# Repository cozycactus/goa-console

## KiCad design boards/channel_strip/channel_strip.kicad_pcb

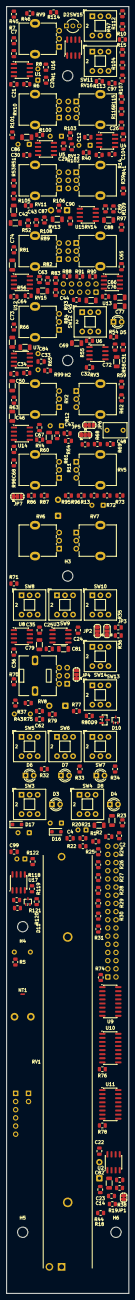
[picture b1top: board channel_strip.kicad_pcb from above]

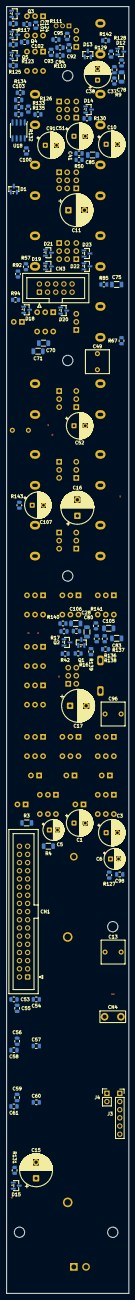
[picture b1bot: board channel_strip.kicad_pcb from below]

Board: 4 copper layers, 38.0 x 400.0 mm, 335 parts (105 on the bottom side), 195 nets, no tracks yet.

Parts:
C1, C3: 220u 25V; CP_Radial_D8.0mm_P3.50mm
C2, C4, C12, C20, C21, C22, C23, C24, C25, C26, C28, C29, C30, C31, C32, C33, C34, C35, C36, C53, C54, C55, C56, C57, C58, C59, C60, C61, C63, C64, C65, C66, C67, C68, C89, C90, C92, C93, C98, C100, C103, C104: 100n; C_0805_2012Metric
C5, C6: 47u 25V; CP_Radial_D6.3mm_P2.50mm
C7, C41: 33p C0G; C_0805_2012Metric
C10, C38, C51, C52, C91, C107: 33u NP 25V; CP_Radial_D8.0mm_P3.50mm
C11, C15, C16, C17: 100u NP 25V; CP_Radial_D10.0mm_P5.00mm
C13, C49, C96: 2.2u film; C_Rect_L7.2mm_W7.2mm_P5.00mm_FKS2_FKP2_MKS2_MKP2
C14, C94, C95: 100p C0G; C_0805_2012Metric
C37: 22p C0G; C_0805_2012Metric
C42, C43, C45: 4n7 C0G; C_1206_3216Metric
C44: 2n2 C0G; C_1206_3216Metric
C46: 10n C0G; C_1206_3216Metric
C47: 22n C0G; C_1206_3216Metric
C48: 150n film; C_Rect_L7.2mm_W4.5mm_P5.00mm_FKS2_FKP2_MKS2_MKP2
C50, C87, C88: 100n C0G; C_1206_3216Metric
C62: 1u; C_0805_2012Metric
C69, C70, C71, C72, C74, C76, C79, C80, C81, C82, C86: 10p C0G; C_1206_3216Metric
C73, C75, C77, C83, C85, C105, C106: 22p C0G; C_1206_3216Metric
C78: 33p C0G; C_1206_3216Metric
C84: 100p C0G; C_1206_3216Metric
C97, C99: 220n; C_0805_2012Metric
C101, C102: 10n; C_0805_2012Metric
CN1: Bus 2x17; IDC-Header_2x17_P2.54mm_Vertical
CN3: Jack board link 2x5; IDC-Header_2x05_P2.54mm_Vertical
CN4: Ground spade 6.3mm; Keystone_1287-ST_FastOn_Tab_6.35mm
D1, D12, D13, D14, D15: BAV99; SOT-23
D2: OL red / SIG green; LED_D3.0mm-3_P2.00mm
D3: PFL red; LED_D3.0mm
D4: ON green; LED_D3.0mm
D5: EQ green; LED_D3.0mm
D6: L-R yellow; LED_D3.0mm
D7: 1-2 yellow; LED_D3.0mm
D8: 3-4 yellow; LED_D3.0mm
D9: BZX84C5V1; SOT-23
D10, D11: BAT54W; SOT-323_SC-70
D16, D17: MBR140SFT1G; D_SOD-123F
D18, D19, D20, D21, D22, D23: BAV199; SOT-23
H1, H2, H3, H4, H5, H6: M3 standoff 11.5 mm; MountingHole_3.2mm_M3
J3: VCA module socket; PinSocket_1x06_P2.54mm_Vertical
J4: VCA control in; PinHeader_1x02_P2.54mm_Vertical
JP1: VCA bypass; SolderJumper-2_P1.3mm_Bridged_RoundedPad1.0x1.5mm
JP2: Aux1/2 pre source; SolderJumper-3_P1.3mm_Bridged12_RoundedPad1.0x1.5mm
JP3: Aux3/4 pre source; SolderJumper-3_P1.3mm_Bridged12_RoundedPad1.0x1.5mm
JP4: Aux5/6 pre source; SolderJumper-3_P1.3mm_Bridged12_RoundedPad1.0x1.5mm
JP5: Insert send source; SolderJumper-3_P1.3mm_Bridged12_RoundedPad1.0x1.5mm
JP6: EQ input; SolderJumper-3_P1.3mm_Bridged12_RoundedPad1.0x1.5mm
JP7: PRE source; SolderJumper-3_P1.3mm_Bridged12_RoundedPad1.0x1.5mm
NT1: AGND-LGND star; NetTie-2_SMD_Pad0.5mm
Q1, Q2: MMBFJ112; SOT-23
Q3, Q4, Q5: MMBT3906; SOT-23
R1, R2, R3, R4: 10R; R_1206_3216Metric
R5: 10R GND cancel; R_0805_2012Metric
R6, R7, R8, R9: 10K 0.1%; R_0805_2012Metric
R10, R112, R115, R121, R142: 1M; R_0805_2012Metric
R11, R71, R73: 75R; R_0805_2012Metric
R12, R13, R35, R36, R37, R47, R68, R72, R116, R117, R118, R122, R123, R125, R143: 47K; R_0805_2012Metric
R14, R134: 470K; R_0805_2012Metric
R15, R16, R17, R19, R34, R43, R69, R75, R77, R79, R80, R124: 4K7; R_0805_2012Metric
R18, R33, R44, R70, R74, R76, R78: 100K; R_0805_2012Metric
R20, R21, R22, R23, R24, R25, R32, R54, R55, R58, R59, R66, R67: 22K; R_0805_2012Metric
R26, R27, R28, R29, R30, R31: 4K7 1%; R_0805_2012Metric
R38, R137, R140: 2K2; R_0805_2012Metric
R39, R99, R126, R127, R128, R129, R130, R131, R135: 1K; R_0805_2012Metric
R40, R41, R120, R138, R141: 10K; R_0805_2012Metric
R42: 220K; R_0805_2012Metric
R45, R46, R84, R93: 2K2 1%; R_0805_2012Metric
R50, R51: 33K; R_0805_2012Metric
R52: 5K6; R_0805_2012Metric
R53: 6K8; R_0805_2012Metric
R56, R57, R100, R103: 4K99 1%; R_0805_2012Metric
R60, R61: 4K22 1%; R_0805_2012Metric
R62, R63, R136, R139: 3K3; R_0805_2012Metric
R64: 1K5; R_0805_2012Metric
R65: 5K1; R_0805_2012Metric
R81, R82, R83, R85, R90, R91, R92, R94: 10K 1%; R_0805_2012Metric
R86, R87: 392R 1%; R_0805_2012Metric
R88, R89, R97, R98, R105, R108: 13K 1%; R_0805_2012Metric
R95, R96: 430R 1%; R_0805_2012Metric
R101, R102: 2K49 1%; R_0805_2012Metric
R104, R107: 330R 1%; R_0805_2012Metric
R106, R109: 5K6 1%; R_0805_2012Metric
R110, R111: 220R; R_0805_2012Metric
R113, R114: 100R; R_0805_2012Metric
R119: 750K; R_0805_2012Metric
R132: 4M99 1%; R_0805_2012Metric
R133: 10M 1%; R_0805_2012Metric
RV1: Fader 10K log 100mm; Potentiometer_Bourns_PTB0143_Slide_100mm
RV2: Aux1 10K log; Potentiometer_Alpha_RD901F-40-00D_Single_Vertical
RV3: Aux2 10K log; Potentiometer_Alpha_RD901F-40-00D_Single_Vertical
RV4: Aux3 10K log; Potentiometer_Alpha_RD901F-40-00D_Single_Vertical
RV5: Aux4 10K log; Potentiometer_Alpha_RD901F-40-00D_Single_Vertical
RV6: Aux5 10K log; Potentiometer_Alpha_RD901F-40-00D_Single_Vertical
RV7: Aux6 10K log; Potentiometer_Alpha_RD901F-40-00D_Single_Vertical
RV8: Pan 10K lin dual CD; Potentiometer_Alps_RK09L_Double_Vertical
RV9: Gain 10K lin CD; Potentiometer_Alpha_RD901F-40-00D_Single_Vertical
RV10: HF 10K lin CD; Potentiometer_Alpha_RD901F-40-00D_Single_Vertical
RV11: HI-MID gain 10K lin CD; Potentiometer_Alpha_RD901F-40-00D_Single_Vertical
RV12: HI-MID freq 10K A dual; Potentiometer_Alpha_RD902F-40-00D_Dual_Vertical
RV13: LO-MID gain 10K lin CD; Potentiometer_Alpha_RD901F-40-00D_Single_Vertical
RV14: LO-MID freq 10K A dual; Potentiometer_Alpha_RD902F-40-00D_Dual_Vertical
RV15: LF 10K lin CD; Potentiometer_Alpha_RD901F-40-00D_Single_Vertical
RV16: HPF freq 10K A dual; Potentiometer_Alpha_RD902F-40-00D_Dual_Vertical
SW3: PFL; SW_Push_2P2T_Toggle_CK_PVA2xxH1xxxxxxV2
SW4: ON; SW_Push_2P2T_Toggle_CK_PVA2xxH1xxxxxxV2
SW5: Assign L-R; SW_Push_2P2T_Toggle_CK_PVA2xxH1xxxxxxV2
SW6: Assign 1-2; SW_Push_2P2T_Toggle_CK_PVA2xxH1xxxxxxV2
SW7: Assign 3-4; SW_Push_2P2T_Toggle_CK_PVA2xxH1xxxxxxV2
SW8: PRE 1-2; SW_Push_2P2T_Toggle_CK_PVA2xxH1xxxxxxV2
SW9: PRE 3-4; SW_Push_2P2T_Toggle_CK_PVA2xxH1xxxxxxV2
SW10: PRE 5-6; SW_Push_2P2T_Toggle_CK_PVA2xxH1xxxxxxV2
SW11: HPF; SW_Push_2P2T_Toggle_CK_PVA2xxH1xxxxxxV2
SW12: EQ; SW_Push_2P2T_Toggle_CK_PVA2xxH1xxxxxxV2
SW13: DIR; SW_Push_2P2T_Toggle_CK_PVA2xxH1xxxxxxV2
SW14: PAN; SW_Push_2P2T_Toggle_CK_PVA2xxH1xxxxxxV2
SW15: Phase; SW_Push_2P2T_Toggle_CK_PVA2xxH1xxxxxxV2
U1, U2, U3, U5, U6, U7, U8, U12, U13, U14, U15: OPA1612; SOIC-8_3.9x4.9mm_P1.27mm
U4, U17, U18: LM393; SOIC-8_3.9x4.9mm_P1.27mm
U9, U10, U11: DG413; SOIC-16_3.9x9.9mm_P1.27mm
U16: OPA1656; SOIC-8_3.9x4.9mm_P1.27mm

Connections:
+5VL: C55.1, C58.1, C61.1, C62.1, D9.3, D10.1, R80.2, SW5.1, SW6.1, SW7.1, U9.12, U10.12, U11.12
+VA: C1.1, C2.1, C20.1, C22.1, C24.1, C29.1, C31.1, C33.1, C35.1, C53.1, C56.1, C59.1, C63.1, C65.1, C67.1, C89.1, C92.1, D10.3, D16.1, D18.2, D19.2, D20.2, D21.2, D22.2, D23.2, J3.4, R1.2, R80.1, U1.8, U2.8, U3.8, U5.8, U6.8, U7.8, U8.8, U9.13, U10.13, U11.13, U12.8, U13.8, U14.8, U15.8, U16.8
+VBUS: CN1.32, CN1.33, CN1.34, R1.1, R3.1
+VL: C5.1, C26.1, C98.1, C101.2, C102.2, C104.1, Q3.2, Q4.2, Q5.2, R3.2, R40.1, R115.1, R117.1, R121.1, R123.1, R132.1, SW3.5, SW4.5, SW5.5, SW6.5, SW7.5, SW12.5, U4.8, U17.8, U18.8
-VA: C3.2, C4.2, C21.2, C23.2, C25.2, C30.2, C32.2, C34.2, C36.2, C54.2, C57.2, C60.2, C64.2, C66.2, C68.2, C90.2, C93.2, D17.2, D18.1, D19.1, D20.1, D21.1, D22.1, D23.1, J3.6, R2.2, U1.4, U2.4, U3.4, U5.4, U6.4, U7.4, U8.4, U9.4, U10.4, U11.4, U12.4, U13.4, U14.4, U15.4, U16.4
-VBUS: CN1.30, CN1.31, R2.1, R4.1
-VL: C6.2, R4.2, SW4.1
A6R: R25.1, SW13.3, SW13.5
AUX1: CN1.24, R20.2
AUX2: CN1.25, R21.2
AUX3: CN1.23, R22.2
AUX4: CN1.22, R23.2
AUX5: CN1.21, R24.2
AUX6: CN1.20, R25.2
BUF1: JP6.3, JP7.1, U7.6, U7.7
DIRSRC: C83.1, R70.1, SW13.1, U8.3
DO_R: CN3.9, D23.3, R73.1, R143.1
DO_T: C52.2, CN3.8, D22.3, R72.1
EQIN: JP6.2, R50.1, RV10.3, SW12.3
EQOUT: C51.2, JP5.1, JP7.3, R68.1, R130.1
EQ_FP: C49.2, C50.1, R65.1, U7.3
EQ_LP: C46.1, R93.1, R98.1, RV14.6, U6.5, U14.1
EQ_MP: C44.1, R84.1, R89.1, RV12.6, U6.3, U12.7
EQ_O6: C73.1, R63.2, R67.1, SW12.1, U7.1
EQ_WHM: R81.1, RV11.2
EQ_WLM: R90.1, RV13.2
FPIN: C82.1, J3.2, JP1.2, R18.1, U2.3
FPOST: C14.1, C15.1, R19.1, R131.1, U2.1
GCANCEL: CN1.26, R5.2
GNDA: C1.2, C2.2, C3.1, C4.1, C12.2, C20.2, C21.1, C22.2, C23.1, C24.2, C25.1, C28.2, C29.2, C30.1, C31.2, C32.1, C33.2, C34.1, C35.2, C36.1, C50.2, C53.2, C54.1, C56.2, C57.1, C59.2, C60.1, C63.2, C64.1, C65.2, C66.1, C67.2, C68.1, C75.2, C77.2, C78.2, C79.2, C80.2, C81.2, C82.2, C83.2, C84.2, C85.2, C89.2, C90.1, C92.2, C93.1, C94.2, C95.2, C100.2, C103.2, C107.2, CN1.2, CN1.4, CN1.6, CN1.8, CN1.10, CN1.12, CN1.14, CN1.16, CN3.3, CN3.5, CN3.7, CN3.10, CN4.1, D16.2, D17.1, J3.5, J4.2, NT1.1, Q1.2, Q2.2, R5.1, R9.2, R10.2, R12.2, R13.2, R14.2, R18.2, R35.2, R36.2, R37.2, R38.2, R41.2, R44.2, R47.2, R52.2, R65.2, R68.2, R70.2, R72.2, R85.2, R86.2, R87.2, R94.2, R95.2, R96.2, R104.2, R107.2, R112.2, R120.2, R134.2, R138.1, R141.1, R143.2, RV1.1, RV2.1, RV3.1, RV4.1, RV5.1, RV6.1, RV7.1, RV8.3, RV8.4, SW3.3, SW13.4, U1.5, U2.5, U5.5, U9.10, U9.15, U10.10, U10.15, U11.10, U11.15, U12.5, U13.3, U14.3, U14.5, U15.3, U15.5
GNDD: C5.2, C6.1, C26.2, C55.2, C58.2, C61.2, C62.2, C97.2, C98.2, C99.2, C104.2, D2.2, D3.1, D4.1, D5.1, D6.1, D7.1, D8.1, D9.1, D11.1, NT1.2, R74.2, R76.2, R78.2, SW4.3, SW5.3, SW6.3, SW7.3, U4.4, U9.5, U10.5, U11.5, U17.4, U18.4, U18.6
GOUT: C37.1, C38.1, C91.1, R46.2, R129.1, R142.2, U1.7
HIN: C38.2, C91.2, R47.1, R100.1, SW11.3
HOUT: JP2.3, JP3.3, JP4.3, JP5.3, JP6.1, SW11.2
INS_SRC: JP5.2, R11.1
IN_R: CN3.2, D19.3, R111.1, R112.1
IN_T: CN3.1, D18.3, R10.1, R110.1
MIXL: CN1.18, U9.2
MIXR: CN1.17, U9.7
MUTEOUT: JP2.1, JP3.1, JP4.1, RV1.3, U3.6, U3.7
unnamed: C10.2, R12.1, R99.1
unnamed: C13.1, RV1.2
unnamed: C41.1, C69.1, R51.1, R54.1, RV10.1, RV11.1, U5.7
unnamed: C42.1, RV10.2
unnamed: C42.2, C43.1, R52.1
unnamed: C43.2, R53.1
unnamed: C45.1, R82.1, U13.1
unnamed: C47.1, R91.1, U14.7
unnamed: C48.1, R62.2, RV15.1
unnamed: C48.2, R63.1, RV15.3
unnamed: C49.1, R64.2
unnamed: C52.1, R71.2
unnamed: C70.1, C71.1, R55.1, R58.1, RV11.3, RV13.1, U6.1
unnamed: C72.1, R59.1, R62.1, R66.1, RV13.3, U6.7
unnamed: C74.1, R83.1, R88.1, RV12.3, U12.1
unnamed: C76.1, R92.1, R97.1, RV14.3, U13.7
unnamed: C87.1, R101.1, R108.1, RV16.6, U15.1
unnamed: C88.1, R102.1, U15.7
unnamed: C96.2, R32.1
unnamed: C16.1, C105.2, R136.1, R137.2, U8.7
unnamed: C17.1, C106.2, R139.1, R140.2, U3.1
unnamed: C107.1, R73.2
unnamed: D1.3, R39.2
unnamed: D3.2, R34.2
unnamed: D4.2, R43.2
unnamed: D5.2, R69.2
unnamed: D6.2, R75.2
unnamed: D7.2, R77.2
unnamed: D8.2, R79.2
unnamed: D12.3, R128.2
unnamed: D13.3, R129.2
unnamed: D14.3, R130.2
unnamed: D15.3, R131.2
unnamed: JP2.2, SW8.1
unnamed: JP3.2, SW9.1
unnamed: JP4.2, SW10.1
unnamed: Q1.1, R16.2, R17.1
unnamed: C28.1, Q1.3, Q2.3, R42.2
unnamed: C81.1, Q2.1, R17.2, U3.5
unnamed: C101.1, Q3.1, R116.2, R117.2
unnamed: Q3.3, R15.1
unnamed: Q4.3, R124.1
unnamed: Q5.1, R125.2
unnamed: R20.1, RV2.2
unnamed: R21.1, RV3.2
unnamed: R22.1, RV4.2
unnamed: R23.1, RV5.2
unnamed: R24.1, RV6.2
unnamed: R26.2, U9.3, U9.14
unnamed: R27.2, U9.6, U9.11
unnamed: R28.2, U10.3, U10.14
unnamed: R29.2, U10.6, U10.11
unnamed: R30.2, U11.3, U11.14
unnamed: R31.2, U11.6, U11.11
unnamed: R45.2, RV9.3
unnamed: R46.1, RV9.1
unnamed: R56.1, R88.2, RV12.2
unnamed: R57.1, R89.2, RV12.5
unnamed: R60.1, R97.2, RV14.2
unnamed: R61.1, R98.2, RV14.5
unnamed: R64.1, RV15.2
unnamed: R86.1, RV12.1
unnamed: R87.1, RV12.4
unnamed: R95.1, RV14.1
unnamed: R96.1, RV14.4
unnamed: R104.1, RV16.1
unnamed: R105.2, R106.1, RV16.2
unnamed: R107.1, RV16.4
unnamed: R108.2, R109.1, RV16.5
unnamed: R122.1, U17.7
unnamed: R126.1, U4.1
unnamed: R127.1, U17.1
unnamed: R135.1, U18.1
unnamed: R32.2, SW3.2
unnamed: R33.1, R34.1, SW3.4
unnamed: R42.1, SW4.2
unnamed: R43.1, SW4.4
unnamed: R75.1, SW5.4
unnamed: R77.1, SW6.4
unnamed: R79.1, SW7.4
unnamed: RV2.3, RV3.3, SW8.2
unnamed: RV4.3, RV5.3, SW9.2
unnamed: RV6.3, RV7.3, SW10.2
unnamed: C86.1, R103.1, R105.1, RV16.3, SW11.1, U5.1
unnamed: C51.1, SW12.2
unnamed: R69.1, SW12.4
unnamed: RV7.2, SW13.2
unnamed: R114.2, SW15.1, SW15.6
unnamed: R6.1, SW15.2
unnamed: R113.2, SW15.3, SW15.4
unnamed: R8.1, SW15.5
unnamed: C78.1, R8.2, R9.1, U1.3
unnamed: C7.1, R6.2, R7.1, U1.2
unnamed: C37.2, R142.1, RV9.2, U1.6
unnamed: C14.2, R19.2, R38.1, U2.2
unnamed: U2.6, U2.7
unnamed: C80.1, R139.2, RV8.5, U3.3
unnamed: C106.1, R140.1, R141.2, U3.2
unnamed: C85.1, R100.2, R101.2, U5.3
unnamed: C86.2, R102.2, R103.2, U5.2
unnamed: C41.2, R50.2, R51.2, R53.2, U5.6
unnamed: C69.2, C70.2, R54.2, R55.2, U6.2
unnamed: C71.2, C72.2, R58.2, R59.2, U6.6
unnamed: C73.2, R66.2, R67.2, U7.2
unnamed: C84.1, R99.2, U7.5
unnamed: R71.1, U8.1, U8.2
unnamed: C79.1, R136.2, RV8.2, U8.5
unnamed: C105.1, R137.1, R138.2, U8.6
unnamed: C75.1, R84.2, R85.1, U12.3
unnamed: C74.2, R81.2, R82.2, R83.2, U12.2
unnamed: C44.2, R56.2, U12.6
unnamed: C45.2, R57.2, U13.2
unnamed: C77.1, R93.2, R94.1, U13.5
unnamed: C76.2, R90.2, R91.2, R92.2, U13.6
unnamed: C46.2, R60.2, U14.2
unnamed: C47.2, R61.2, U14.6
unnamed: C87.2, R106.2, U15.2
unnamed: C88.2, R109.2, U15.6
unnamed: C94.1, R110.2, U16.3
unnamed: R113.1, U16.1, U16.2
unnamed: C95.1, R111.2, U16.5
unnamed: R114.1, U16.6, U16.7
unnamed: R119.2, R120.1, U17.3
unnamed: C99.1, R121.2, R127.2, U17.5
unnamed: R132.2, R133.1, U18.3
OL_A: D2.1, R15.2
OL_HOLD: C97.1, R115.2, R126.2, R135.2, U4.5
OL_K: R116.1, R125.1, U4.7
OL_NN: C103.1, D1.1, D12.1, D13.1, D14.1, D15.1, R133.2, R134.1
PANL: C16.2, R26.1, R36.1, SW14.1
PANR: C17.2, R27.1, R37.1, SW14.4
PFL: CN1.27, SW3.1
PFLDET: CN1.29, R33.2
PK: C12.1, D1.2, D12.2, D13.2, D14.2, D15.2, R14.1, U4.2
POST: C15.2, R35.1, RV8.1, RV8.6, SW8.3, SW9.3, SW10.3, SW14.3, SW14.6
PRE: C11.2, C96.1, R13.1, R16.1
PRESRC: C11.1, JP7.2, R39.1, R118.1
RECV: C7.2, R7.2, R45.1, R128.1, U1.1
RET_RAW: C10.1, CN3.6, D20.3
RTE_12: R76.1, SW6.2, U10.1, U10.8, U10.9, U10.16
RTE_34: R78.1, SW7.2, U11.1, U11.8, U11.9, U11.16
RTE_LR: R74.1, SW5.2, U9.1, U9.8, U9.9, U9.16
SEND: CN3.4, D21.3, R11.2
SIG_A: D2.3, R124.2
SIG_B: C102.1, Q4.1, Q5.3, R122.2, R123.2
SIG_IN: D11.3, R118.2, U17.2
SUB1: CN1.15, U10.2
SUB2: CN1.13, U10.7
SUB3: CN1.11, U11.2
SUB4: CN1.9, U11.7
SUBSRC_L: R28.1, R30.1, SW14.2
SUBSRC_R: R29.1, R31.1, SW14.5
VCAIN: C13.2, J3.1, JP1.1
VCA_CTRL: J3.3, J4.1, R44.1
VREF: C100.1, R40.2, R41.1, R119.1, U4.3, U4.6, U17.6, U18.2, U18.5

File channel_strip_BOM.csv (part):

"Qty","Value","Footprint","MPN","DNP","References"
"2","220u 25V","Capacitor_THT:CP_Radial_D8.0mm_P3.50mm","Rubycon 35ZLH220MEFC8X11.5 (35V)","","C1 C3"
"38","100n","Capacitor_SMD:C_0805_2012Metric","Samsung CL21B104KBCNNNC (X7R 50V)","","C2 C4 C12 C20 C21 C22 C23 C24 C25 C26 C28 C29 C30 C31 C32 C33 C34 C35 C36 C53 C54 C55 C56 C57 C58 C59 C60 C61 C63 C64 C65 C66 C67 C68 C89 C90 C92 C93"
"2","47u 25V","Capacitor_THT:CP_Radial_D6.3mm_P2.50mm","Panasonic EEU-FR1H470 (50V)","","C5 C6"
"2","33p C0G","Capacitor_SMD:C_0805_2012Metric","KEMET C1206C330J5GACTU","","C7 C41"
"5","33u NP 25V","Capacitor_THT:CP_Radial_D8.0mm_P3.50mm","Nichicon UES1E330MPM (MUSE ES)","","C10 C38 C51 C52 C91"
"4","100u NP 25V","Capacitor_THT:CP_Radial_D10.0mm_P5.00mm","Nichicon UES1E101MPM (MUSE ES)","","C11 C15 C16 C17"
"3","2.2u film","Capacitor_THT:C_Rect_L7.2mm_W7.2mm_P5.00mm_FKS2_FKP2_MKS2_MKP2","WIMA MKS2C042201K00KSSD (PET 63V)","","C13 C49 C96"
"3","100p C0G","Capacitor_SMD:C_0805_2012Metric","KEMET C1206C101J5GACTU","","C14 C94 C95"
"1","22p C0G","Capacitor_SMD:C_0805_2012Metric","KEMET C1206C220J5GACTU","","C37"
"3","4n7 C0G","Capacitor_SMD:C_1206_3216Metric","KEMET C1206C472J5GACTU","","C42 C43 C45"
"1","2n2 C0G","Capacitor_SMD:C_1206_3216Metric","KEMET C1206C222J5GACTU","","C44"
"1","10n C0G","Capacitor_SMD:C_1206_3216Metric","KEMET C1206C103J5GACTU","","C46"
"1","22n C0G","Capacitor_SMD:C_1206_3216Metric","KEMET C1206C223J5GACTU","","C47"
"1","150n film","Capacitor_THT:C_Rect_L7.2mm_W4.5mm_P5.00mm_FKS2_FKP2_MKS2_MKP2","WIMA MKS2D031501C00KSSD (PET 100V; 3.5 x 8.5 x 7.2, the 63 V KSSD code has no stock)","","C48"
"3","100n C0G","Capacitor_SMD:C_1206_3216Metric","Murata GRM31C5C1H104JA01L","","C50 C87 C88"
"1","1u","Capacitor_SMD:C_0805_2012Metric","Murata GRM21BR71H105KA12L (X7R 50V)","","C62"
"11","10p C0G","Capacitor_SMD:C_1206_3216Metric","KEMET C1206C100J5GACTU","","C69 C70 C71 C72 C74 C76 C79 C80 C81 C82 C86"
"5","22p C0G","Capacitor_SMD:C_1206_3216Metric","KEMET C1206C220J5GACTU","","C73 C75 C77 C83 C85"
"1","33p C0G","Capacitor_SMD:C_1206_3216Metric","KEMET C1206C330J5GACTU","","C78"
"1","100p C0G","Capacitor_SMD:C_1206_3216Metric","KEMET C1206C101J5GACTU","","C84"
"1","220n","Capacitor_SMD:C_0805_2012Metric","Samsung CL21B224KBFNNNE (X7R 50V)","","C97"
"1","Bus 2x17","Connector_IDC:IDC-Header_2x17_P2.54mm_Vertical","Wurth 61203421621 (2x17 box header)","","CN1"
"1","Jack board link 2x5","Connector_IDC:IDC-Header_2x05_P2.54mm_Vertical","Wurth 61201021621 (2x5 box header)","","CN3"
"1","Ground spade 6.3mm","goa-console:Keystone_1287-ST_FastOn_Tab_6.35mm","Keystone 1287-ST","","CN4"
"1","1N4148","Diode_THT:D_DO-35_SOD27_P7.62mm_Horizontal","Vishay 1N4148-TAP","","D1"
"1","OL red","LED_THT:LED_D3.0mm","Kingbright WP710A10ID","","D2"
"1","PFL red","LED_THT:LED_D3.0mm","Kingbright WP710A10ID","","D3"
"1","ON green","LED_THT:LED_D3.0mm","Kingbright WP710A10GD","","D4"
"1","EQ green","LED_THT:LED_D3.0mm","Kingbright WP710A10GD","","D5"
"1","L-R yellow","LED_THT:LED_D3.0mm","Kingbright WP710A10YD","","D6"
"1","1-2 yellow","LED_THT:LED_D3.0mm","Kingbright WP710A10YD","","D7"
"1","3-4 yellow","LED_THT:LED_D3.0mm","Kingbright WP710A10YD","","D8"
"1","BZX84C5V1","Package_TO_SOT_SMD:SOT-23","Nexperia BZX84-C5V1,215","","D9"
"1","BAT54W","Package_TO_SOT_SMD:SOT-323_SC-70","Nexperia BAT54W,115","","D10"
"1","VCA module socket","Connector_PinSocket_2.54mm:PinSocket_1x06_P2.54mm_Vertical","","DNP","J3"
"1","VCA control in","Connector_PinHeader_2.54mm:PinHeader_1x02_P2.54mm_Vertical","","DNP","J4"
"2","MMBFJ112","Package_TO_SOT_SMD:SOT-23","onsemi MMBFJ112","","Q1 Q2"
"2","10R","Resistor_SMD:R_0805_2012Metric","Panasonic ERJ-P06J100V","","R1 R2"
"2","10R","Resistor_SMD:R_0805_2012Metric","","","R3 R4"
"1","10R GND cancel","Resistor_SMD:R_0805_2012Metric","","","R5"
"4","10K 0.1%","Resistor_SMD:R_0805_2012Metric","Panasonic ERA-6AEB103V","","R6 R7 R8 R9"
"3","1M","Resistor_SMD:R_0805_2012Metric","","","R10 R112 R115"
"2","75R","Resistor_SMD:R_0805_2012Metric","Panasonic ERJ-P06J750V","","R11 R71"
"8","47K","Resistor_SMD:R_0805_2012Metric","","","R12 R13 R35 R36 R37 R47 R68 R72"
"1","470K","Resistor_SMD:R_0805_2012Metric","","","R14"
"11","4K7","Resistor_SMD:R_0805_2012Metric","","","R15 R16 R17 R19 R34 R43 R69 R75 R77 R79 R80"
"6","100K","Resistor_SMD:R_0805_2012Metric","","","R18 R33 R70 R74 R76 R78"
"13","22K","Resistor_SMD:R_0805_2012Metric","","","R20 R21 R22 R23 R24 R25 R32 R54 R55 R58 R59 R66 R67"
"10","4K7 1%","Resistor_SMD:R_0805_2012Metric","","","R26 R27 R28 R29 R30 R31 R56 R57 R60 R61"
"1","2K2","Resistor_SMD:R_0805_2012Metric","","","R38"
"2","1K","Resistor_SMD:R_0805_2012Metric","","","R39 R99"
"2","10K","Resistor_SMD:R_0805_2012Metric","","","R40 R41"
"1","220K","Resistor_SMD:R_0805_2012Metric","","","R42"
"1","100K","Resistor_SMD:R_0805_2012Metric","","DNP","R44"
"4","2K2 1%","Resistor_SMD:R_0805_2012Metric","","","R45 R46 R84 R93"
"2","33K","Resistor_SMD:R_0805_2012Metric","","","R50 R51"
"1","5K6","Resistor_SMD:R_0805_2012Metric","","","R52"
"1","6K8","Resistor_SMD:R_0805_2012Metric","","","R53"
"2","3K3","Resistor_SMD:R_0805_2012Metric","","","R62 R63"
"1","1K5","Resistor_SMD:R_0805_2012Metric","","","R64"
"1","5K1","Resistor_SMD:R_0805_2012Metric","","","R65"
"1","75R","Resistor_SMD:R_0805_2012Metric","","","R73"
"8","10K 1%","Resistor_SMD:R_0805_2012Metric","","","R81 R82 R83 R85 R90 R91 R92 R94"
"4","430R 1%","Resistor_SMD:R_0805_2012Metric","","","R86 R87 R95 R96"
"6","13K 1%","Resistor_SMD:R_0805_2012Metric","","","R88 R89 R97 R98 R105 R108"
"2","4K99 1%","Resistor_SMD:R_0805_2012Metric","","","R100 R103"
"2","2K49 1%","Resistor_SMD:R_0805_2012Metric","","","R101 R102"
"2","330R 1%","Resistor_SMD:R_0805_2012Metric","","","R104 R107"
"2","5K6 1%","Resistor_SMD:R_0805_2012Metric","","","R106 R109"
"2","220R","Resistor_SMD:R_0805_2012Metric","","","R110 R111"
"2","100R","Resistor_SMD:R_0805_2012Metric","","","R113 R114"
"1","Fader 10K log 100mm","goa-console:Potentiometer_Bourns_PTB0143_Slide_100mm","Bourns PTB0143-2010BPA103","","RV1"
"1","Aux1 10K log","Potentiometer_THT:Potentiometer_Alpha_RD901F-40-00D_Single_Vertical","Alpha RD901F-40-15R1-A10K","","RV2"
"1","Aux2 10K log","Potentiometer_THT:Potentiometer_Alpha_RD901F-40-00D_Single_Vertical","Alpha RD901F-40-15R1-A10K","","RV3"
"1","Aux3 10K log","Potentiometer_THT:Potentiometer_Alpha_RD901F-40-00D_Single_Vertical","Alpha RD901F-40-15R1-A10K","","RV4"
"1","Aux4 10K log","Potentiometer_THT:Potentiometer_Alpha_RD901F-40-00D_Single_Vertical","Alpha RD901F-40-15R1-A10K","","RV5"
"1","Aux5 10K log","Potentiometer_THT:Potentiometer_Alpha_RD901F-40-00D_Single_Vertical","Alpha RD901F-40-15R1-A10K","","RV6"
"1","Aux6 10K log","Potentiometer_THT:Potentiometer_Alpha_RD901F-40-00D_Single_Vertical","Alpha RD901F-40-15R1-A10K","","RV7"
"1","Pan 10K lin dual CD","Potentiometer_THT:Potentiometer_Alps_RK09L_Double_Vertical","ALPS RK09L1240015","","RV8"
"1","Gain 10K lin CD","Potentiometer_THT:Potentiometer_Alpha_RD901F-40-00D_Single_Vertical","Alpha RD901F-40-15R1-B10K-0CD (centre detent)","","RV9"
"1","HF 10K lin CD","Potentiometer_THT:Potentiometer_Alpha_RD901F-40-00D_Single_Vertical","Alpha RD901F-40-15R1-B10K-0CD (centre detent)","","RV10"
"1","HI-MID gain 10K lin CD","Potentiometer_THT:Potentiometer_Alpha_RD901F-40-00D_Single_Vertical","Alpha RD901F-40-15R1-B10K-0CD (centre detent)","","RV11"
"1","HI-MID freq 10K A dual","Potentiometer_THT:Potentiometer_Alpha_RD902F-40-00D_Dual_Vertical","Alpha RD902F-40-15R1-A10K (dual, log)","","RV12"
"1","LO-MID gain 10K lin CD","Potentiometer_THT:Potentiometer_Alpha_RD901F-40-00D_Single_Vertical","Alpha RD901F-40-15R1-B10K-0CD (centre detent)","","RV13"
"1","LO-MID freq 10K A dual","Potentiometer_THT:Potentiometer_Alpha_RD902F-40-00D_Dual_Vertical","Alpha RD902F-40-15R1-A10K (dual, log)","","RV14"
"1","LF 10K lin CD","Potentiometer_THT:Potentiometer_Alpha_RD901F-40-00D_Single_Vertical","Alpha RD901F-40-15R1-B10K-0CD (centre detent)","","RV15"
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
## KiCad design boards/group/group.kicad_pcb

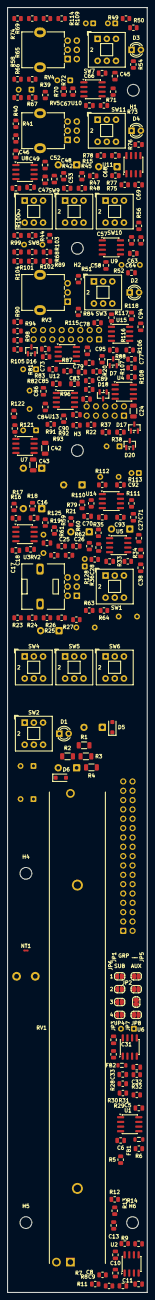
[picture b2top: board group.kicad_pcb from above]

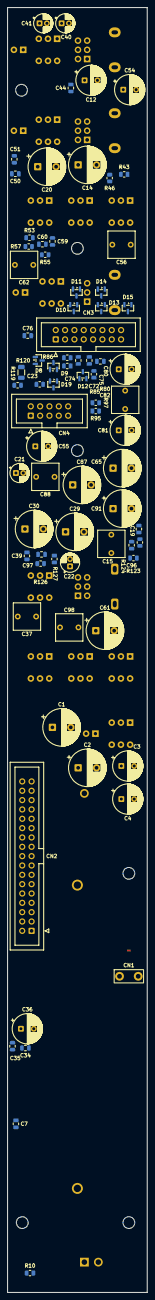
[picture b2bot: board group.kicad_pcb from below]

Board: 4 copper layers, 38.0 x 349.5 mm, 298 parts (76 on the bottom side), 167 nets, no tracks yet.

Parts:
C1, C2: 220u 25V; CP_Radial_D10.0mm_P5.00mm
C3, C4: 47u 25V; CP_Radial_D8.0mm_P3.50mm
C5, C6, C10, C11, C16, C17, C27, C28, C31, C32, C48, C49, C57, C58, C66, C67, C68, C69, C74, C75, C83, C84, C92, C93, C94, C95: 100n; C_0805_2012Metric
C7, C13, C19, C33, C38, C44, C45, C50, C51, C59, C63, C70, C71, C76, C77, C85, C89: 100p C0G; C_0805_2012Metric
C8, C9, C34, C35: 22p C0G 5%; C_0805_2012Metric
C12, C36, C54, C55, C80, C81: 33u NP 25V; CP_Radial_D8.0mm_P3.50mm
C14, C20, C29, C30, C61, C65, C87, C91: 100u NP 25V; CP_Radial_D10.0mm_P5.00mm
C15, C37, C56, C62, C82, C88, C98: 2.2u film; C_Rect_L7.2mm_W7.2mm_P5.00mm_FKS2_FKP2_MKS2_MKP2
C18, C25, C26, C39, C60, C64, C86, C90: 10p C0G; C_0805_2012Metric
C21, C22, C40, C41: 10u NP 25V; CP_Radial_D5.0mm_P2.00mm
C23, C24, C42, C43: 1u; C_1206_3216Metric
C46, C47, C52, C53, C72, C73, C78, C79: 33p C0G; C_0805_2012Metric
C96, C97: 22p C0G; C_0805_2012Metric
CN1: Ground spade 6.3mm; Keystone_1287-ST_FastOn_Tab_6.35mm
CN2: Bus 2x17; IDC-Header_2x17_P2.54mm_Vertical
CN3: Jack board link 2x8; IDC-Header_2x08_P2.54mm_Vertical
CN4: Jack board link 2 2x5; IDC-Header_2x05_P2.54mm_Vertical
D1: Sub AFL red; LED_D3.0mm
D2: Aux AFL red; LED_D3.0mm
D3: Return PFL red; LED_D3.0mm
D4: Return 2 PFL red; LED_D3.0mm
D5, D6: MBR140SFT1G; D_SOD-123F
D7, D8, D9, D10, D11, D12, D13, D14, D15, D16, D17, D18, D19, D20: BAV199; SOT-23
FB1, FB2: Ferrite 220R@100MHz; L_0805_2012Metric
H1, H2, H3, H4, H5, H6: M3 standoff 11.5 mm; MountingHole_3.2mm_M3
JP1: SUB 1 select; SolderJumper-2_P1.3mm_Open_RoundedPad1.0x1.5mm
JP2: SUB 2 select; SolderJumper-2_P1.3mm_Open_RoundedPad1.0x1.5mm
JP3: SUB 3 select; SolderJumper-2_P1.3mm_Open_RoundedPad1.0x1.5mm
JP4: SUB 4 select; SolderJumper-2_P1.3mm_Open_RoundedPad1.0x1.5mm
JP5: AUX 1 select; SolderJumper-2_P1.3mm_Open_RoundedPad1.0x1.5mm
JP6: AUX 2 select; SolderJumper-2_P1.3mm_Open_RoundedPad1.0x1.5mm
JP7: AUX 3 select; SolderJumper-2_P1.3mm_Open_RoundedPad1.0x1.5mm
JP8: AUX 4 select; SolderJumper-2_P1.3mm_Open_RoundedPad1.0x1.5mm
NT1: AGND-LGND star; NetTie-2_SMD_Pad0.5mm
R1, R2, R3, R4: 10R; R_1206_3216Metric
R5: 10R GND cancel; R_0805_2012Metric
R6, R23, R24, R59, R60, R61, R62, R63, R64, R99, R100, R101, R102, R103, R104: 4K7 1%; R_0805_2012Metric
R7, R8, R9, R10, R29, R30, R31, R32: 2K2 0.1%; R_0805_2012Metric
R11, R14: 75R; R_0805_2012Metric
R12, R15, R20, R21, R22, R49, R50, R54, R58, R89, R90, R94, R98: 47K; R_0805_2012Metric
R13: 1K; R_0805_2012Metric
R16, R26, R33, R37, R51, R55, R67, R91, R95, R107: 100K; R_0805_2012Metric
R17: 47R; R_0805_2012Metric
R18, R27, R34, R38, R52, R56, R68, R92, R96, R108: 4K7; R_0805_2012Metric
R19, R124, R127: 2K2; R_0805_2012Metric
R25, R36: 22K; R_0805_2012Metric
R28: 22K 1%; R_0805_2012Metric
R35, R53, R57, R93, R97: DNF (2K2 = +10 dB); R_0805_2012Metric
R39, R44, R69, R74, R79, R84, R109, R114: 1M; R_0805_2012Metric
R40, R41, R42, R43, R45, R46, R47, R48, R80, R81, R82, R83, R85, R86, R87, R88: 10K 0.1%; R_0805_2012Metric
R65, R66, R105, R106: 43K; R_0805_2012Metric
R70, R71, R75, R76, R110, R111, R115, R116: 220R; R_0805_2012Metric
R72, R73, R77, R78, R112, R113, R117, R118: 100R; R_0805_2012Metric
R119, R120, R121, R122: 22R; R_0805_2012Metric
R123, R126: 3K3; R_0805_2012Metric
R125, R128: 10K; R_0805_2012Metric
RV1: Sub fader 10K log 100mm; Potentiometer_Bourns_PTB0143_Slide_100mm
RV2: Sub pan 10K lin dual CD; Potentiometer_Alps_RK09L_Double_Vertical
RV3: Aux master 10K log; Potentiometer_Alpha_RD901F-40-00D_Single_Vertical
RV4: Return level 10K log dual; Potentiometer_Alpha_RD902F-40-00D_Dual_Vertical
RV5: Return 2 level 10K log dual; Potentiometer_Alpha_RD902F-40-00D_Dual_Vertical
SW1: Sub to MIX; SW_Push_2P2T_Toggle_CK_PVA2xxH1xxxxxxV2
SW2: Sub AFL; SW_Push_2P2T_Toggle_CK_PVA2xxH1xxxxxxV2
SW3: Aux AFL; SW_Push_2P2T_Toggle_CK_PVA2xxH1xxxxxxV2
SW4: Return MIX; SW_Push_2P2T_Toggle_CK_PVA2xxH1xxxxxxV2
SW5: Return 1-2; SW_Push_2P2T_Toggle_CK_PVA2xxH1xxxxxxV2
SW6: Return 3-4; SW_Push_2P2T_Toggle_CK_PVA2xxH1xxxxxxV2
SW7: Return PFL; SW_Push_2P2T_Toggle_CK_PVA2xxH1xxxxxxV2
SW8: Return 2 MIX; SW_Push_2P2T_Toggle_CK_PVA2xxH1xxxxxxV2
SW9: Return 2 1-2; SW_Push_2P2T_Toggle_CK_PVA2xxH1xxxxxxV2
SW10: Return 2 3-4; SW_Push_2P2T_Toggle_CK_PVA2xxH1xxxxxxV2
SW11: Return 2 PFL; SW_Push_2P2T_Toggle_CK_PVA2xxH1xxxxxxV2
U1, U2, U3, U5, U6, U8, U9, U12, U13: OPA1612; SOIC-8_3.9x4.9mm_P1.27mm
U4, U7: DRV135; SOIC-8_3.9x4.9mm_P1.27mm
U10, U11, U14, U15: OPA1656; SOIC-8_3.9x4.9mm_P1.27mm

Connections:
+VA: C1.1, C5.1, C10.1, C16.1, C23.1, C27.1, C31.1, C42.1, C48.1, C57.1, C66.1, C68.1, C74.1, C83.1, C92.1, C94.1, D5.1, D7.2, D8.2, D9.2, D10.2, D11.2, D12.2, D13.2, D14.2, D15.2, D16.2, D17.2, D18.2, D19.2, D20.2, R1.2, U1.8, U2.8, U3.8, U4.6, U5.8, U6.8, U7.6, U8.8, U9.8, U10.8, U11.8, U12.8, U13.8, U14.8, U15.8
+VBUS: CN2.32, CN2.33, CN2.34, R1.1, R3.1
+VL: C3.1, R3.2, SW2.5, SW3.5, SW7.5, SW11.5
-VA: C2.2, C6.2, C11.2, C17.2, C24.2, C28.2, C32.2, C43.2, C49.2, C58.2, C67.2, C69.2, C75.2, C84.2, C93.2, C95.2, D6.2, D7.1, D8.1, D9.1, D10.1, D11.1, D12.1, D13.1, D14.1, D15.1, D16.1, D17.1, D18.1, D19.1, D20.1, R2.2, U1.4, U2.4, U3.4, U4.5, U5.4, U6.4, U7.5, U8.4, U9.4, U10.4, U11.4, U12.4, U13.4, U14.4, U15.4
-VBUS: CN2.30, CN2.31, R2.1, R4.1
-VL: C4.2, R4.2
AUX1: CN2.24, JP5.2
AUX2: CN2.25, JP6.2
AUX3: CN2.23, JP7.2
AUX4: CN2.22, JP8.2
AUX_SEL: FB2.1, JP5.1, JP6.1, JP7.1, JP8.1
A_AFLC: C98.2, R36.1
A_AFLJ: R36.2, SW3.2
A_MIX: C34.1, C36.1, R30.2, U6.7
A_ON: C41.2, CN3.9, D12.3, U7.2
A_OP: C40.2, CN3.8, D11.3, U7.7
A_OUT: C38.1, C98.1, R34.1, U5.7, U7.4
A_PT: C36.2, RV3.3
A_SUM: C33.1, R28.1, R29.1, U6.1
A_W: C37.1, RV3.2
GCANCEL: CN2.26, R5.2, U1.3, U1.5, U6.3
GC_BUF: R9.1, R31.1, U1.1, U1.2
GNDA: C1.2, C2.1, C5.2, C6.1, C9.2, C10.2, C11.1, C13.2, C16.2, C17.1, C18.2, C23.2, C24.1, C25.2, C26.2, C27.2, C28.1, C31.2, C32.1, C35.2, C39.2, C42.2, C43.1, C44.2, C45.2, C47.2, C48.2, C49.1, C50.2, C51.2, C53.2, C57.2, C58.1, C60.2, C64.2, C66.2, C67.1, C68.2, C69.1, C70.2, C71.2, C73.2, C74.2, C75.1, C76.2, C77.2, C79.2, C83.2, C84.1, C86.2, C90.2, C92.2, C93.1, C94.2, C95.1, CN1.1, CN2.2, CN2.4, CN2.6, CN2.8, CN2.10, CN2.12, CN2.14, CN2.16, CN3.2, CN3.4, CN3.7, CN3.10, CN3.13, CN3.16, CN4.3, CN4.6, CN4.7, CN4.8, CN4.9, CN4.10, D5.2, D6.1, NT1.1, R5.1, R10.2, R12.2, R15.2, R16.2, R19.2, R20.2, R21.2, R22.2, R32.2, R33.2, R35.2, R39.2, R43.2, R44.2, R48.2, R49.2, R50.2, R51.2, R53.2, R54.2, R55.2, R57.2, R58.2, R69.2, R74.2, R79.2, R83.2, R84.2, R88.2, R89.2, R90.2, R91.2, R93.2, R94.2, R95.2, R97.2, R98.2, R109.2, R114.2, R125.2, R128.2, RV1.1, RV2.3, RV2.4, RV3.1, RV4.1, RV4.4, RV5.1, RV5.4, SW1.3, SW1.6, SW2.3, SW3.3, SW4.3, SW4.6, SW5.3, SW5.6, SW6.3, SW6.6, SW7.3, SW8.3, SW8.6, SW9.3, SW9.6, SW10.3, SW10.6, SW11.3, U4.3, U7.3
GNDD: C3.2, C4.1, D1.1, D2.1, D3.1, D4.1, NT1.2
MIXL: CN2.18, SW1.1, SW4.1, SW8.1
MIXR: CN2.17, SW1.4, SW4.4, SW8.4
unnamed: C12.2, R12.1, R13.1
unnamed: C14.1, R14.2
unnamed: C19.1, R17.1, R18.1, U3.1
unnamed: C20.1, R17.2
unnamed: C21.1, R119.2
unnamed: C22.1, R120.2
unnamed: C40.1, R121.2
unnamed: C41.1, R122.2
unnamed: D1.2, R27.2
unnamed: D2.2, R38.2
unnamed: D3.2, R68.2
unnamed: D4.2, R108.2
unnamed: R23.2, SW1.2
unnamed: R24.2, SW1.5
unnamed: R26.1, R27.1, SW2.4
unnamed: R37.1, R38.1, SW3.4
unnamed: R59.2, SW4.2
unnamed: R60.2, SW4.5
unnamed: R61.2, SW5.2
unnamed: R62.2, SW5.5
unnamed: R63.2, SW6.2
unnamed: R64.2, SW6.5
unnamed: R67.1, R68.1, SW7.4
unnamed: R99.2, SW8.2
unnamed: R100.2, SW8.5
unnamed: R101.2, SW9.2
unnamed: R102.2, SW9.5
unnamed: R103.2, SW10.2
unnamed: R104.2, SW10.5
unnamed: R107.1, R108.1, SW11.4
unnamed: C7.2, FB1.2, R6.2, U1.6
unnamed: C9.1, R9.2, R10.1, U2.3
unnamed: C8.2, R7.2, R8.1, U2.2
unnamed: C13.1, R13.2, U2.5
unnamed: R14.1, U2.6, U2.7
unnamed: C15.2, C18.1, R16.1, U3.3
unnamed: C19.2, R18.2, R19.1, U3.2
unnamed: C96.1, R124.1, R125.1, U3.6
unnamed: R119.1, U4.8
unnamed: R120.1, U4.1
unnamed: C97.1, R127.1, R128.1, U5.2
unnamed: C37.2, C39.1, R33.1, U5.5
unnamed: C38.2, R34.2, R35.1, U5.6
unnamed: C33.2, FB2.2, R28.2, U6.2
unnamed: C35.1, R31.2, R32.1, U6.5
unnamed: C34.2, R29.2, R30.1, U6.6
unnamed: R121.1, U7.8
unnamed: R122.1, U7.1
unnamed: C47.1, R42.2, R43.1, U8.3
unnamed: C46.1, R40.2, R41.1, U8.2
unnamed: C53.1, R47.2, R48.1, U8.5
unnamed: C52.1, R45.2, R46.1, U8.6
unnamed: C56.2, C60.1, R51.1, U9.3
unnamed: C59.2, R52.2, R53.1, U9.2
unnamed: C62.2, C64.1, R55.1, U9.5
unnamed: C63.2, R56.2, R57.1, U9.6
unnamed: C44.1, R70.2, U10.3
unnamed: R72.1, U10.1, U10.2
unnamed: C45.1, R71.2, U10.5
unnamed: R73.1, U10.6, U10.7
unnamed: C50.1, R75.2, U11.3
unnamed: R77.1, U11.1, U11.2
unnamed: C51.1, R76.2, U11.5
unnamed: R78.1, U11.6, U11.7
unnamed: C73.1, R82.2, R83.1, U12.3
unnamed: C72.1, R80.2, R81.1, U12.2
unnamed: C79.1, R87.2, R88.1, U12.5
unnamed: C78.1, R85.2, R86.1, U12.6
unnamed: C82.2, C86.1, R91.1, U13.3
unnamed: C85.2, R92.2, R93.1, U13.2
unnamed: C88.2, C90.1, R95.1, U13.5
unnamed: C89.2, R96.2, R97.1, U13.6
unnamed: C70.1, R110.2, U14.3
unnamed: R112.1, U14.1, U14.2
unnamed: C71.1, R111.2, U14.5
unnamed: R113.1, U14.6, U14.7
unnamed: C76.1, R115.2, U15.3
unnamed: R117.1, U15.1, U15.2
unnamed: C77.1, R116.2, U15.5
unnamed: R118.1, U15.6, U15.7
PFL: CN2.27, SW2.1, SW3.1, SW7.1, SW11.1
PFLDET: CN2.29, R26.2, R37.2, R67.2, R107.2
RT2_BL: C85.1, C87.1, R92.1, U13.1
RT2_BR: C89.1, C91.1, R96.1, U13.7
RT2_L: C72.2, C80.1, R81.2, U12.1
RT2_L_RB: R80.1, R113.2
RT2_L_TB: R82.1, R112.2
RT2_PFLJ: R105.2, R106.2, SW11.2
RT2_PREL: C80.2, R89.1, R105.1, RV5.3
RT2_PRER: C81.2, R90.1, R106.1, RV5.6
RT2_R: C78.2, C81.1, R86.2, U12.7
RT2_RTNL: C87.2, R94.1, R99.1, R101.1, R103.1
RT2_RTNR: C91.2, R98.1, R100.1, R102.1, R104.1
RT2_R_RB: R85.1, R118.2
RT2_R_TB: R87.1, R117.2
RT2_WL: C82.1, RV5.2
RT2_WR: C88.1, RV5.5
RT_BL: C59.1, C61.1, R52.1, U9.1
RT_BR: C63.1, C65.1, R56.1, U9.7
RT_L: C46.2, C54.1, R41.2, U8.1
RT_L_RB: R40.1, R73.2
RT_L_TB: R42.1, R72.2
RT_PFLJ: R65.2, R66.2, SW7.2
RT_PREL: C54.2, R49.1, R65.1, RV4.3
RT_PRER: C55.2, R50.1, R66.1, RV4.6
RT_R: C52.2, C55.1, R46.2, U8.7
RT_RTNL: C61.2, R54.1, R59.1, R61.1, R63.1
RT_RTNR: C65.2, R58.1, R60.1, R62.1, R64.1
RT_R_RB: R45.1, R78.2
RT_R_TB: R47.1, R77.2
RT_WL: C56.1, RV4.2
RT_WR: C62.1, RV4.5
Return2_LR: CN4.2, D18.3, R109.1, R111.1
Return2_LT: CN4.1, D17.3, R79.1, R110.1
Return2_RR: CN4.5, D20.3, R114.1, R116.1
Return2_RT: CN4.4, D19.3, R84.1, R115.1
Return_LR: CN3.12, D14.3, R69.1, R71.1
Return_LT: CN3.11, D13.3, R39.1, R70.1
Return_RR: CN3.15, D16.3, R74.1, R76.1
Return_RT: CN3.14, D15.3, R44.1, R75.1
SUB1: CN2.15, JP1.2, SW5.1, SW9.1
SUB2: CN2.13, JP2.2, SW5.4, SW9.4
SUB3: CN2.11, JP3.2, SW6.1, SW10.1
SUB4: CN2.9, JP4.2, SW6.4, SW10.4
SUB_RETRAW: C12.1, CN3.3, D8.3
SUB_SEL: FB1.1, JP1.1, JP2.1, JP3.1, JP4.1
SUB_SEND: CN3.1, D7.3, R11.2
S_AFLJ: R25.2, SW2.2
S_MIX: C8.1, R8.2, R11.1, U2.1
S_ON: C22.2, CN3.6, D10.3, U4.2
S_OP: C21.2, CN3.5, D9.3, U4.7
S_PANL: C29.2, R21.1, R23.1
S_PANR: C30.2, R22.1, R24.1
S_PBL: C29.1, C96.2, R123.2, R124.2, U3.7
S_PBR: C30.1, C97.2, R126.2, R127.2, U5.1
S_POST: C20.2, R20.1, R25.1, RV2.1, RV2.6, U4.4
S_PRE: C14.2, R15.1, RV1.3
S_PWL: C25.1, R123.1, RV2.2, U3.5
S_PWR: C26.1, R126.1, RV2.5, U5.3
S_SUM: C7.1, R6.1, R7.1, U1.7
S_W: C15.1, RV1.2

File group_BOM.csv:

"Qty","Value","Footprint","MPN","DNP","References"
"2","220u 25V","Capacitor_THT:CP_Radial_D10.0mm_P5.00mm","Nichicon UHE1V221MPD6 (35V)","","C1 C2"
"2","47u 25V","Capacitor_THT:CP_Radial_D8.0mm_P3.50mm","Nichicon UPW1J470MPD (63V)","","C3 C4"
"18","100n","Capacitor_SMD:C_0805_2012Metric","Samsung CL21B104KBCNNNC (X7R 50V)","","C5 C6 C10 C11 C16 C17 C27 C28 C31 C32 C48 C49 C57 C58 C66 C67 C68 C69"
"11","100p C0G","Capacitor_SMD:C_0805_2012Metric","KEMET C0805C101J5GACTU","","C7 C13 C19 C33 C38 C44 C45 C50 C51 C59 C63"
"4","22p C0G 5%","Capacitor_SMD:C_0805_2012Metric","KEMET C0805C220J5GACTU","","C8 C9 C34 C35"
"4","33u NP 25V","Capacitor_THT:CP_Radial_D8.0mm_P3.50mm","Nichicon UES1E330MPM (MUSE ES)","","C12 C36 C54 C55"
"6","100u NP 25V","Capacitor_THT:CP_Radial_D10.0mm_P5.00mm","Nichicon UES1E101MPM (MUSE ES)","","C14 C20 C29 C30 C61 C65"
"4","2.2u film","Capacitor_THT:C_Rect_L7.2mm_W7.2mm_P5.00mm_FKS2_FKP2_MKS2_MKP2","WIMA MKS2C042201K00KSSD (PET 63V)","","C15 C37 C56 C62"
"6","10p C0G","Capacitor_SMD:C_0805_2012Metric","KEMET C0805C100J5GACTU","","C18 C25 C26 C39 C60 C64"
"4","10u NP 25V","Capacitor_THT:CP_Radial_D5.0mm_P2.00mm","Panasonic ECE-A1EN100U","","C21 C22 C40 C41"
"4","1u","Capacitor_SMD:C_1206_3216Metric","Samsung CL31B105KBHNNNE (X7R 50V)","","C23 C24 C42 C43"
"4","33p C0G","Capacitor_SMD:C_0805_2012Metric","KEMET C0805C330J5GACTU","","C46 C47 C52 C53"
"1","Ground spade 6.3mm","goa-console:Keystone_1287-ST_FastOn_Tab_6.35mm","Keystone 1287-ST","","CN1"
"1","Bus 2x17","Connector_IDC:IDC-Header_2x17_P2.54mm_Vertical","Wurth 61203421621 (2x17 box header)","","CN2"
"1","Jack board link 2x8","Connector_IDC:IDC-Header_2x08_P2.54mm_Vertical","Wurth 61201621621 (2x8 box header)","","CN3"
"1","Sub AFL red","LED_THT:LED_D3.0mm","Kingbright WP710A10ID","","D1"
"1","Aux AFL red","LED_THT:LED_D3.0mm","Kingbright WP710A10ID","","D2"
"1","Return PFL red","LED_THT:LED_D3.0mm","Kingbright WP710A10ID","","D3"
"2","Ferrite 220R@100MHz","Inductor_SMD:L_0805_2012Metric","Murata BLM21PG221SN1D","","FB1 FB2"
"2","10R","Resistor_SMD:R_0805_2012Metric","Panasonic ERJ-P06J100V","","R1 R2"
"2","10R","Resistor_SMD:R_0805_2012Metric","","","R3 R4"
"1","10R GND cancel","Resistor_SMD:R_0805_2012Metric","","","R5"
"9","4K7 1%","Resistor_SMD:R_0805_2012Metric","","","R6 R23 R24 R59 R60 R61 R62 R63 R64"
"8","2K2 0.1%","Resistor_SMD:R_0805_2012Metric","Panasonic ERA-6AEB222V","","R7 R8 R9 R10 R29 R30 R31 R32"
"1","75R","Resistor_SMD:R_0805_2012Metric","Panasonic ERJ-P06J750V","","R11"
"9","47K","Resistor_SMD:R_0805_2012Metric","","","R12 R15 R20 R21 R22 R49 R50 R54 R58"
"1","1K","Resistor_SMD:R_0805_2012Metric","","","R13"
"1","75R","Resistor_SMD:R_0805_2012Metric","","","R14"
"7","100K","Resistor_SMD:R_0805_2012Metric","","","R16 R26 R33 R37 R51 R55 R67"
"1","47R","Resistor_SMD:R_0805_2012Metric","","","R17"
"7","4K7","Resistor_SMD:R_0805_2012Metric","","","R18 R27 R34 R38 R52 R56 R68"
"1","2K2","Resistor_SMD:R_0805_2012Metric","","","R19"
"2","22K","Resistor_SMD:R_0805_2012Metric","","","R25 R36"
"1","22K 1%","Resistor_SMD:R_0805_2012Metric","","","R28"
"3","DNF (2K2 = +10 dB)","Resistor_SMD:R_0805_2012Metric","","DNP","R35 R53 R57"
"4","1M","Resistor_SMD:R_0805_2012Metric","","","R39 R44 R69 R74"
"8","10K 0.1%","Resistor_SMD:R_0805_2012Metric","Panasonic ERA-6AEB103V","","R40 R41 R42 R43 R45 R46 R47 R48"
"2","43K","Resistor_SMD:R_0805_2012Metric","","","R65 R66"
"4","220R","Resistor_SMD:R_0805_2012Metric","","","R70 R71 R75 R76"
"4","100R","Resistor_SMD:R_0805_2012Metric","","","R72 R73 R77 R78"
"1","Sub fader 10K log 100mm","goa-console:Potentiometer_Bourns_PTB0143_Slide_100mm","Bourns PTB0143-2010BPA103","","RV1"
"1","Sub pan 10K lin dual CD","Potentiometer_THT:Potentiometer_Alps_RK09L_Double_Vertical","ALPS RK09L1240015","","RV2"
"1","Aux master 10K log","Potentiometer_THT:Potentiometer_Alpha_RD901F-40-00D_Single_Vertical","Alpha RD901F-40-15R1-A10K","","RV3"
"1","Return level 10K log dual","Potentiometer_THT:Potentiometer_Alpha_RD902F-40-00D_Dual_Vertical","Alpha RD902F-40-15R1-A10K (dual, log)","","RV4"
"1","Sub to MIX","Button_Switch_THT:SW_Push_2P2T_Toggle_CK_PVA2xxH1xxxxxxV2","C&K PVA2 EE H1 1.7N V2","","SW1"
"1","Sub AFL","Button_Switch_THT:SW_Push_2P2T_Toggle_CK_PVA2xxH1xxxxxxV2","C&K PVA2 EE H1 1.7N V2","","SW2"
"1","Aux AFL","Button_Switch_THT:SW_Push_2P2T_Toggle_CK_PVA2xxH1xxxxxxV2","C&K PVA2 EE H1 1.7N V2","","SW3"
"1","Return MIX","Button_Switch_THT:SW_Push_2P2T_Toggle_CK_PVA2xxH1xxxxxxV2","C&K PVA2 EE H1 1.7N V2","","SW4"
"1","Return 1-2","Button_Switch_THT:SW_Push_2P2T_Toggle_CK_PVA2xxH1xxxxxxV2","C&K PVA2 EE H1 1.7N V2","","SW5"
"1","Return 3-4","Button_Switch_THT:SW_Push_2P2T_Toggle_CK_PVA2xxH1xxxxxxV2","C&K PVA2 EE H1 1.7N V2","","SW6"
"1","Return PFL","Button_Switch_THT:SW_Push_2P2T_Toggle_CK_PVA2xxH1xxxxxxV2","C&K PVA2 EE H1 1.7N V2","","SW7"
"7","OPA1612","Package_SO:SOIC-8_3.9x4.9mm_P1.27mm","TI OPA1612AIDR","","U1 U2 U3 U5 U6 U8 U9"
"2","DRV135","Package_SO:SOIC-8_3.9x4.9mm_P1.27mm","TI DRV135UA","","U4 U7"
"2","OPA1656","Package_SO:SOIC-8_3.9x4.9mm_P1.27mm","TI OPA1656IDR","","U10 U11"
